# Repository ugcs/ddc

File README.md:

Drone Show Software
=========

Drone Show Software is software designed for drone shows, allowing flight path planning as well as control of dozens of drones simultaneously in a synchronized manner.

This repository contains guidelines for building and setting up the drones, WiFi and LED modules as well as adding and setting up RTK GPS units.

Description
-----------

Drone Show Software requires a custom Pixhawk firmware due to special flight mode and commands it uses. Pixhawk hardware or copies thereof can be used. These autopilots are widely available and available for purchase from most drone part dealers.

Drones can be used with standard GPS units, but to ensure flight precision that is necessary for drone shows, we recommend using RTK GPS units.

For establishing reliable communication between multiple drones, we suggest using 5GHz WiFi modules onboard drones rather than standard (433MHz) telemetry data links.
For drone show purposes, drones can be equipped with LED modules or other show elements that can be controlled via PWM servo signal.

- [**Drone_hardware**](./Drone_hardware) contains all the information for assembling, manufacturing and configuring drones, WiFi modules and LED payloads.

 - [**3D_Printing**](./3D_Printing) contains STL files for 3D printing GPS and Flight controller cases.
 
 - [**Airborne 5GHz WiFi**](./Drone_hardware/Airborne_5GHz_WiFi) contains guidelines and schematics to assemble Airborne 5GHz WiFi modules.

 - [**Fireball LED payload**](./Drone_hardware/Fireball_LED_payload) contains guidelines and schematics to assemble Fireball LED payloads.

 - [**PCB-KiCad**](./Drone_hardware/PCB-KiCad/lib) contains PCB source project files for [KiCad EDA](http://kicad.org/)

- [**Software_tools**](./Software_tools) contains all the necessary software tools to cofigure the drones and run the show.

 - [**DDC_ConfigTool**](./Software_tools/DDC_ConfigTool) this tool is used to easily upload fimrmware and do accelerometer and compass calibration on many drones.
 
 - [**Radio_updater**](./Software_tools/Radio_updater) used to upload 433MHz radio firmware to secondary channel telemetry data links.

 - [**RTK_Tool**](./Software_tools/RTK_Tool) used to broadcast RTK GPS corrections to the drones.

 - [**SITL_simulation**](./Software_tools/SITL_simulation) is used to perform simulated drone show flights.

- [**Animation_samples**](./Animation_samples) contains animation samples.

System requirements
-------------------

System requirements for Drone Show Software:

- *Operating system:* Windows 7 with SP1 or later; Windows 8; Windows 10.
- *CPU:* Intel Core i7 or better.
- *Memory:* Minimum 8 GB of RAM or more.
- *Hard drive:* SSD 120GB. Recommended 256GB or more.
- *Graphics hardware:* Graphics card with DirectX 9 support (shader model 2.0). Any card made since 2004 should work.
- *Network:* TCP/IPv4 network stack, WiFi or Ethernet. Recommended Ethernet.
- *Screen resolution:* FullHD screen.

Licence
-------

All contents except third party ones are licensed under [Creative Commons Attribution-NonCommercial-NoDerivatives 4.0 International License](https://creativecommons.org/licenses/by-nc-nd/4.0/).

Further information
-------------------

This repository is maintained by SPH Engineering, developers of UgCS ground control software for drones.

If you have any questions about this project, feel free to reach out to us at <support@ugcs.com>.

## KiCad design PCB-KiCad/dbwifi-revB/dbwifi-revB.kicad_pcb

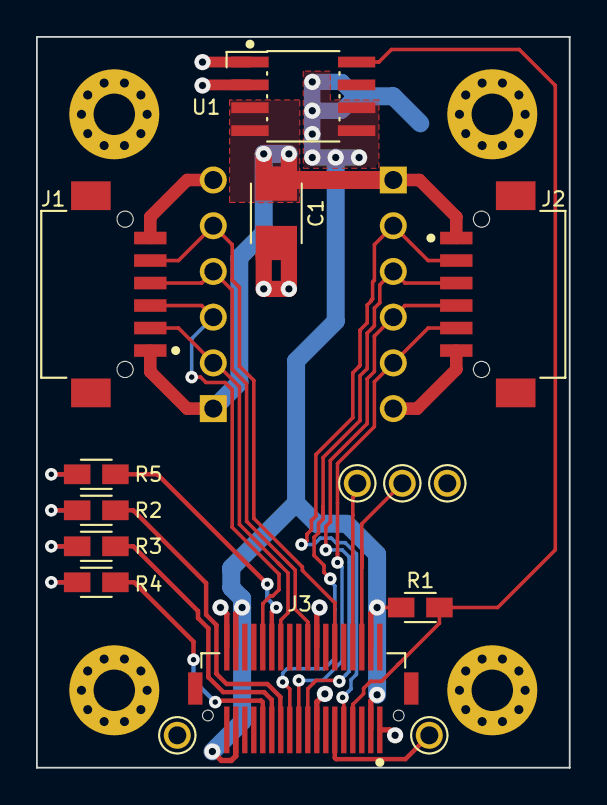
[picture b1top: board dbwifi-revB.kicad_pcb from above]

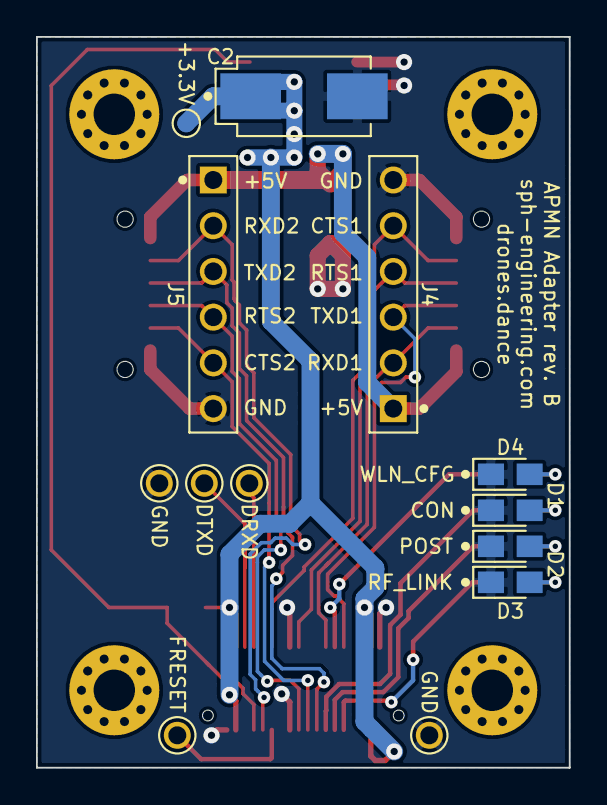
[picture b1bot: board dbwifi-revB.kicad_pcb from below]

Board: 2 copper layers, 29.6 x 40.6 mm, 23 parts (13 on the bottom side), 23 nets.

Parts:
C1: 10u; CAPC3216X180M
C2: 100u; CAPPM7343X310M
D1, D2, D3, D4: LED0603; LEDC1608X90M
J1, J2: [DF13-6P-1.25H]; HIROSE_DF13-6P-1.25H
J3: DF12-4.0-36DP-0.5V; HIROSE_DF12-4.0-36DP-0.5V
J4, J5: DS1021-1x6S; CONNFLY_DS1021-1X6S
R1: 249k; RESC1608X55M
R2, R3, R4, R5: 340; RESC1608X55M
TP1: FRESET; TP-TH-1
TP2, TP5: GND; TP-TH-1
TP3: +3.3V; TP-SM-1
TP4: DTXD; TP-TH-1
TP6: DRXD; TP-TH-1
U1: TPS76733QD; SOIC127P600X175-8M

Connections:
+3V3: C2.1, J3.3, J3.4, J3.33, J3.34, R1.2, TP3.1, U1.5, U1.6
+5V: C1.2, J1.1, J2.1, J4.1, J5.1, U1.3, U1.4
/CTS1: J1.5, J3.12, J4.5
/CTS2: J2.5, J3.19, J5.5
/DRXD: J3.8, TP6.1
/DTXD: J3.6, TP4.1
/FRESET: J3.11, TP1.1
/LED_CON: J3.23, R2.1
/LED_POST: J3.25, R3.1
/LED_RF_LINK: J3.27, R4.1
/LED_WLN_CFG: J3.26, R5.1
/RTS1: J1.4, J3.18, J4.4
/RTS2: J2.4, J3.17, J5.4
/RXD1: J1.2, J3.24, J4.2
/RXD2: J2.2, J3.9, J5.2
/TXD1: J1.3, J3.28, J4.3
/TXD2: J2.3, J3.21, J5.3
/~RESET: J3.7, R1.1, U1.8
GND: C1.1, C2.2, D1.1, D2.1, D3.1, D4.1, J1.6, J2.6, J3.1, J3.15, J3.16, J3.36, J4.6, J5.6, TP2.1, TP5.1, U1.1, U1.2
unnamed: D1.2, R2.2
unnamed: D2.2, R3.2
unnamed: D3.2, R4.2
unnamed: D4.2, R5.2

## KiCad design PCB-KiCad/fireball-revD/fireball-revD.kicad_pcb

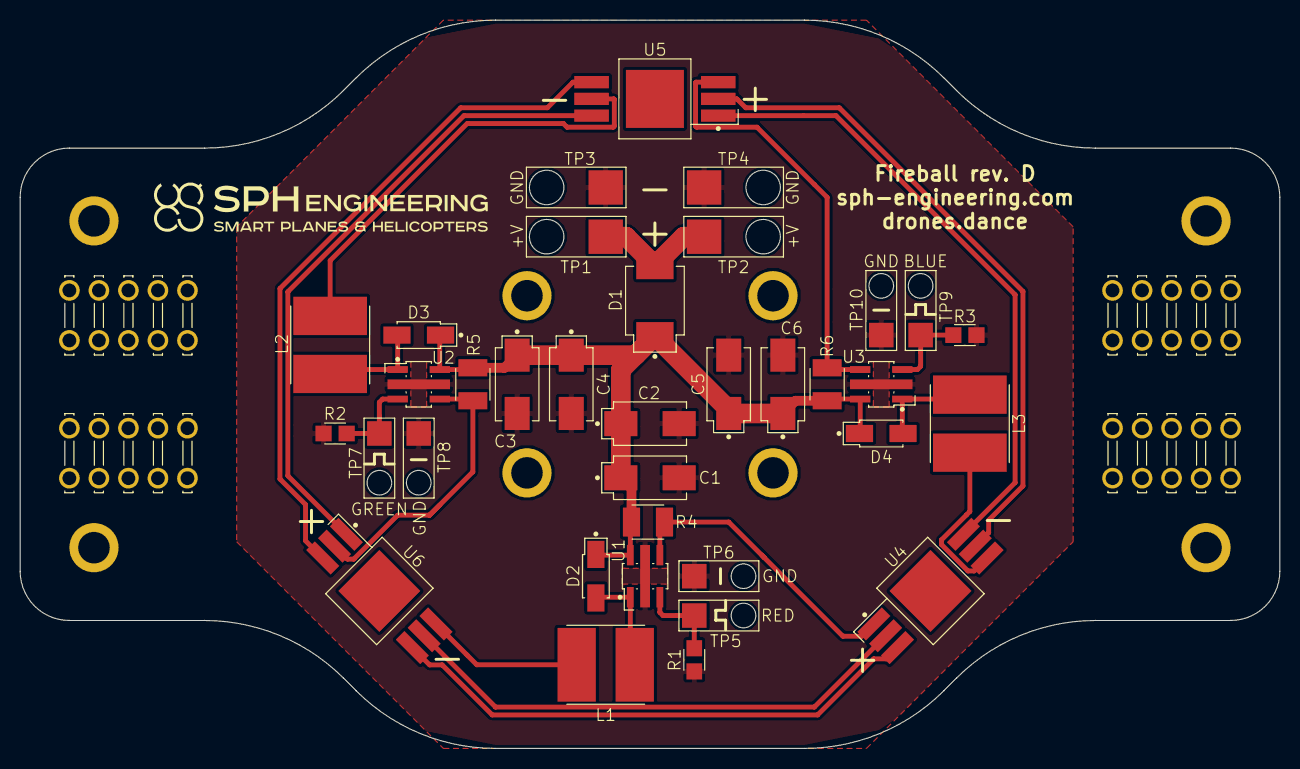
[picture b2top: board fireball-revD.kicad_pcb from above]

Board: 2 copper layers, 128.0 x 74.0 mm, 64 parts (0 on the bottom side), 21 nets.

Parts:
C1, C2, C3, C4, C5, C6: 47u 35V; CAPPM7343X310M
D1: MBRS540T3G; DIOM6958X241M
D2, D3, D4: SS14; DIOM4326X290M
J1, J2, J3, J4, J5, J6, J7, J8, J9, J10, J11, J12, J13, J14, J15, J16, J17, J18, J19, J20: [63849-1]; TE_63849-1
L1, L2, L3: MCSD75-470KU; INDC7870X550M
MH1, MH2, MH3, MH4, MH5, MH6, MH7, MH8: MH-3.2-5
R1, R2, R3: DNP; RESC2013X65M
R4, R5, R6: ERJ14RSFR15U; RESC3126X65M
TP1, TP2: +V; MISC_TPH-3.5-SM-Q3.5
TP3, TP4: GND; MISC_TPH-3.5-SM-Q3.5
TP5: RED; MISC_TPH-2.5-SM-Q2.5
TP6, TP8, TP10: GND; MISC_TPH-2.5-SM-Q2.5
TP7: GREEN; MISC_TPH-2.5-SM-Q2.5
TP9: BLUE; MISC_TPH-2.5-SM-Q2.5
U1, U2, U3: PT4115E; SOTFL150P435X160-5M
U4, U5, U6: JH-9RGB14G45; SOP170P1440X520-7M
svg2mod: G***; SPH-5

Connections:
+V: C1.1, C2.1, C3.1, C4.1, C5.1, C6.1, D1.1, D2.1, D3.1, D4.1, R4.1, R5.1, R6.1, U1.5, U2.5, U3.5
/B+: R6.2, U3.4, U5.3
/B-: L3.2, U4.4
/G+: R5.2, U2.4, U6.2
/G-: L2.2, U5.5
/PB: R3.2, TP9.1, U3.3
/PG: R2.2, TP7.1, U2.3
/PR: R1.2, TP5.1, U1.3
/R+: R4.2, U1.4, U4.1
/R-: L1.2, U6.6
GND: C1.2, C2.2, C3.2, C4.2, C5.2, C6.2, R1.1, R2.1, R3.1, TP3.1, TP4.1, TP6.1, TP8.1, TP10.1, U1.2, U2.2, U3.2
unnamed: D1.2, TP1.1, TP2.1
unnamed: D2.2, L1.1, U1.1
unnamed: D3.2, L2.1, U2.1
unnamed: D4.2, L3.1, U3.1
unnamed: U4.2, U6.5
unnamed: U4.3, U6.4
unnamed: U4.5, U5.2
unnamed: U4.6, U5.1
unnamed: U5.4, U6.3
unnamed: U5.6, U6.1

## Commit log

2017-09-06 Intial set of documents
2017-09-06 Removed APM from supported autopilots
2017-09-07 remove old WiFi doc's
2017-09-07 Change WiFi firmware file name
2017-09-07 Change link to firmware in WiFi module manual
2017-09-07 Publish smaller version of drone assembly instructions
2017-10-06 RTK Corrections broadcasting through MP
2017-11-30 Update LED board
2018-04-10 Add dual-band Wi-Fi adapter schematic and PCB
2018-04-10 Minor fixes in schematics
2018-04-17 Update documents
2018-04-18 Fix the Assembly Instruction
2018-04-27 Move to the proper folder.
2018-04-27 Update system requirements.
2018-05-04 Add PCB project files for KiCad
2018-05-04 Minor fixes in PCB file
2018-05-10 Add Wi-Fi related documents.
2018-05-16 Create SITL
2018-05-17 Readme fix
2018-05-17 Change folders structure.
    Change folders structure.
2018-06-25 Path-generation
    new ver. UgCS-DDC_3.0_Path-generation!_pub
2018-07-09 Update
    Update
2018-07-18 Fix links
2018-07-18 Really fix the links
2018-07-18 Dot added
2018-09-11 Wi-Fi adapter: Remove not populated elements from BOM
2018-10-12 Added assembly drawing (FireBall-revD and wifi-revB)
2018-10-17 Minor fix in DBWiFi PCB
2018-11-01 Update README.md
    Update readme
2018-11-12 Wi-Fi adapter: Add stencil gerber files
2018-11-12 Hardware: Fix KiCad projects
2019-04-05 Update SITL archive (add proper sitl build)
2019-04-25 Added missing cfg file, fixed net ID and naming
2019-04-25 Updated frequency range
2019-04-25 Added python scripts
2019-04-25 Fixed frame rate division error
2019-05-09 Added antenna mount file for 3D printing
2019-07-08 Update links.
2019-08-13 Add exportpath for Blender 2.80
2019-08-16 Remove Dropix from offered autopilots.
2019-10-04 SITL version update to 3.3.1 DSS release.
2019-10-10 added animations
    added animations
2019-10-10 added animation
    added animation
2019-10-17 added LED revF
    added LED revF
2019-11-21 Add encryption key for communication channel.
2019-12-19 Add information for cooling radiator placement.
2020-03-13 added PATH3 export script
2020-03-13 removed Blender 2.79 export script
2020-03-13 renamed Blender 2.8 export script
2020-10-07 Added new BOM
2020-12-31 Added LED info
2021-11-07 Update README.md
    https://forum.kicad.info/t/warning-avoid-all-links-to-kicad-pcb-org-use-kicad-org/31521
